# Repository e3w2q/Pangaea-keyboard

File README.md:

# Pangaea

Parts adjustable keyboard

## What is Pangaea?

Column staggered keyboards differ in the way the columns are shifted and the thumb keys are placed, depending on the designer's assumed finger size and design philosophy.

Pangaea is a column staggered keyboard that allows you to adjust the key layout for the pinky and thumb areas.

https://user-images.githubusercontent.com/50942793/145424793-fb12e412-2e66-4725-97fb-f4ba11a33d6f.mp4

## Link

[ホワイトペーパー](whitepaper_jp.md), [White Paper](whitepaper_en.md)

[ビルドガイド](build_guide_jp.md), [Build Guide](build_guide_en.md)

[パーツリスト](bom_list_jp.md)

[Firmware](firmware/)

[PCB](design/)

[Gerbers](products/)

## License

* firmware: GPLv3
* Garber files: CC-BY-NC
* other files: MIT

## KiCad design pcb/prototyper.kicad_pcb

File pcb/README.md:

# Pangaea PCB Data

Some design data are not included.

“Further, we have to be prepared always for the possibility that each new discovery, no matter what science furnishes it, may modify the conclusions we draw.” 

Alfred Wegener, *The Origins of Continents and Oceans*

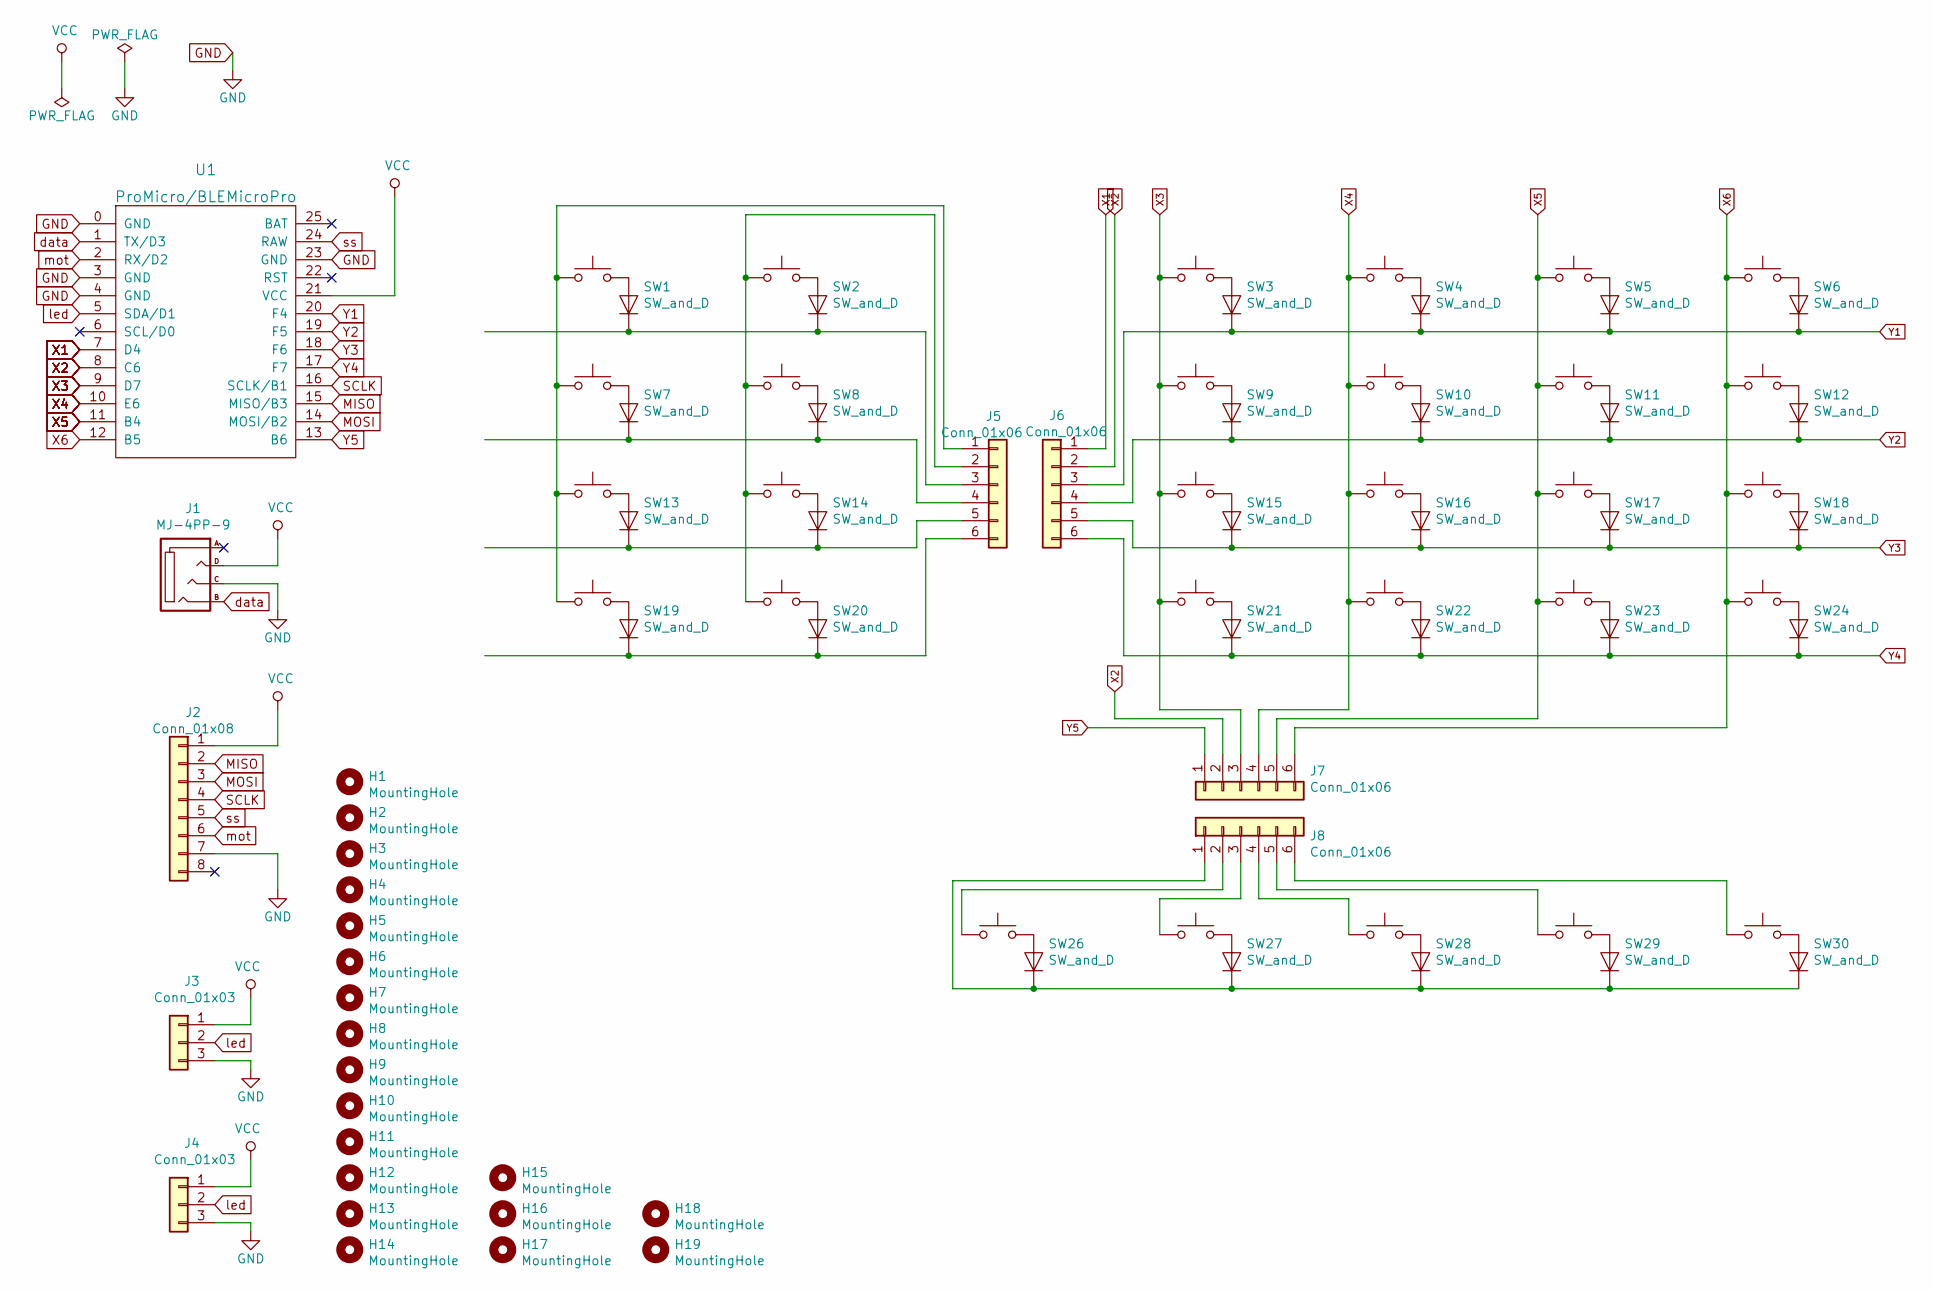
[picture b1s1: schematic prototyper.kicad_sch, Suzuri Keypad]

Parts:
H1, H2, H3, H4, H5, H6, H7, H8, H9, H10, H11, H12, H13, H14: MountingHole; M2_spacer
H15, H16, H17, H18, H19: MountingHole; M1.4_tapping_Hole_rev2
J1: MJ-4PP-9; MJ-4PP-9_reversible
J2: Conn_01x08; PinHeader_1x08_P2.54mm_Vertical_rev2
J3, J4: Conn_01x03; StripLED_rev3
J5, J6, J7, J8: Conn_01x06; PinHeader_1x06_P2.54mm_Vertical_rev2
SW1, SW2, SW3, SW4, SW5, SW6, SW7, SW8, SW9, SW10, SW11, SW12, SW13, SW14, SW15, SW16, SW17, SW18, SW19, SW20, SW21, SW22, SW23, SW24, SW26, SW27, SW28, SW29, SW30: SW_and_D; CherryMX_MidHeight_Choc_Hotswap_Reversible_with_Diode
U1: ProMicro/BLEMicroPro; ArduinoProMicro_ConThrough_Reversible

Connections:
GND: J1.C, J2.7, J3.3, J4.3, U1.0 (GND), U1.3 (GND), U1.4 (GND), U1.23 (GND)
MISO: J2.2, U1.15 (MISO/B3)
MOSI: J2.3, U1.14 (MOSI/B2)
unnamed: J5.1, SW1.1, SW7.1, SW13.1, SW19.1
unnamed: J5.2, SW2.1, SW8.1, SW14.1, SW20.1
unnamed: J5.3, SW1.2, SW2.2
unnamed: J5.4, SW7.2, SW8.2
unnamed: J5.5, SW13.2, SW14.2
unnamed: J5.6, SW19.2, SW20.2
unnamed: J8.1, SW26.2, SW27.2, SW28.2, SW29.2, SW30.2
unnamed: J8.2, SW26.1
unnamed: J8.3, SW27.1
unnamed: J8.4, SW28.1
unnamed: J8.5, SW29.1
unnamed: J8.6, SW30.1
SCLK: J2.4, U1.16 (SCLK/B1)
VCC: J1.D, J2.1, J3.1, J4.1, U1.21 (VCC)
X1: J6.1, U1.7 (D4)
X2: J6.2, J7.2, U1.8 (C6)
X3: J7.3, SW3.1, SW9.1, SW15.1, SW21.1, U1.9 (D7)
X4: J7.4, SW4.1, SW10.1, SW16.1, SW22.1, U1.10 (E6)
X5: J7.5, SW5.1, SW11.1, SW17.1, SW23.1, U1.11 (B4)
X6: J7.6, SW6.1, SW12.1, SW18.1, SW24.1, U1.12 (B5)
Y1: J6.3, SW3.2, SW4.2, SW5.2, SW6.2, U1.20 (F4)
Y2: J6.4, SW9.2, SW10.2, SW11.2, SW12.2, U1.19 (F5)
Y3: J6.5, SW15.2, SW16.2, SW17.2, SW18.2, U1.18 (F6)
Y4: J6.6, SW21.2, SW22.2, SW23.2, SW24.2, U1.17 (F7)
Y5: J7.1, U1.13 (B6)
data: J1.B, U1.1 (TX/D3)
led: J3.2, J4.2, U1.5 (SDA/D1)
mot: J2.6, U1.2 (RX/D2)
ss: J2.5, U1.24 (RAW)

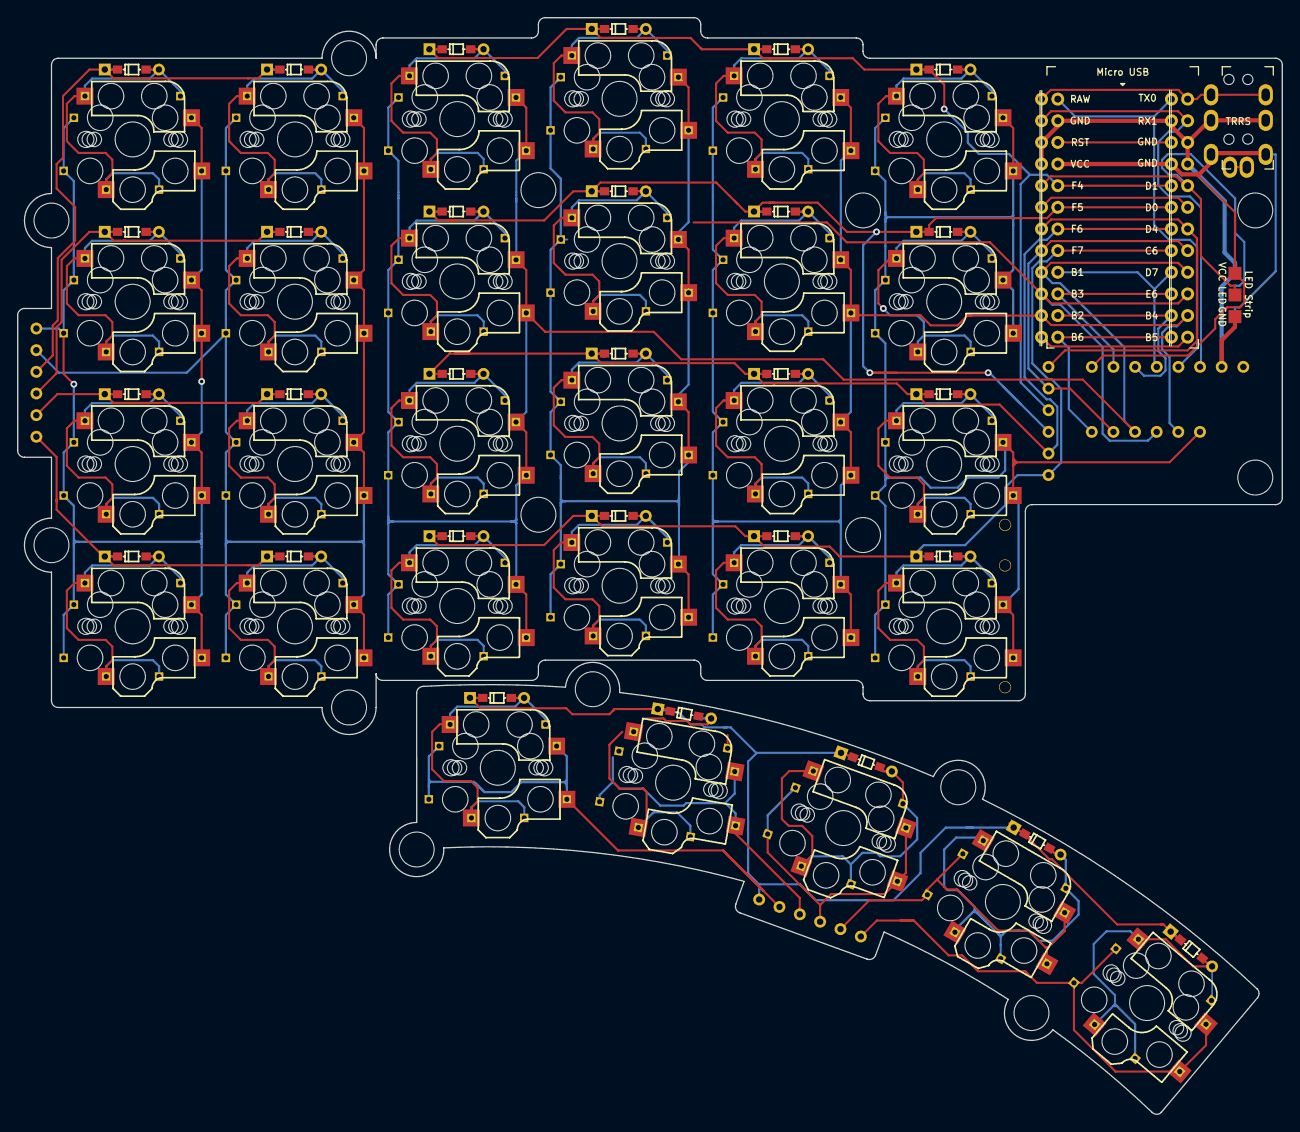
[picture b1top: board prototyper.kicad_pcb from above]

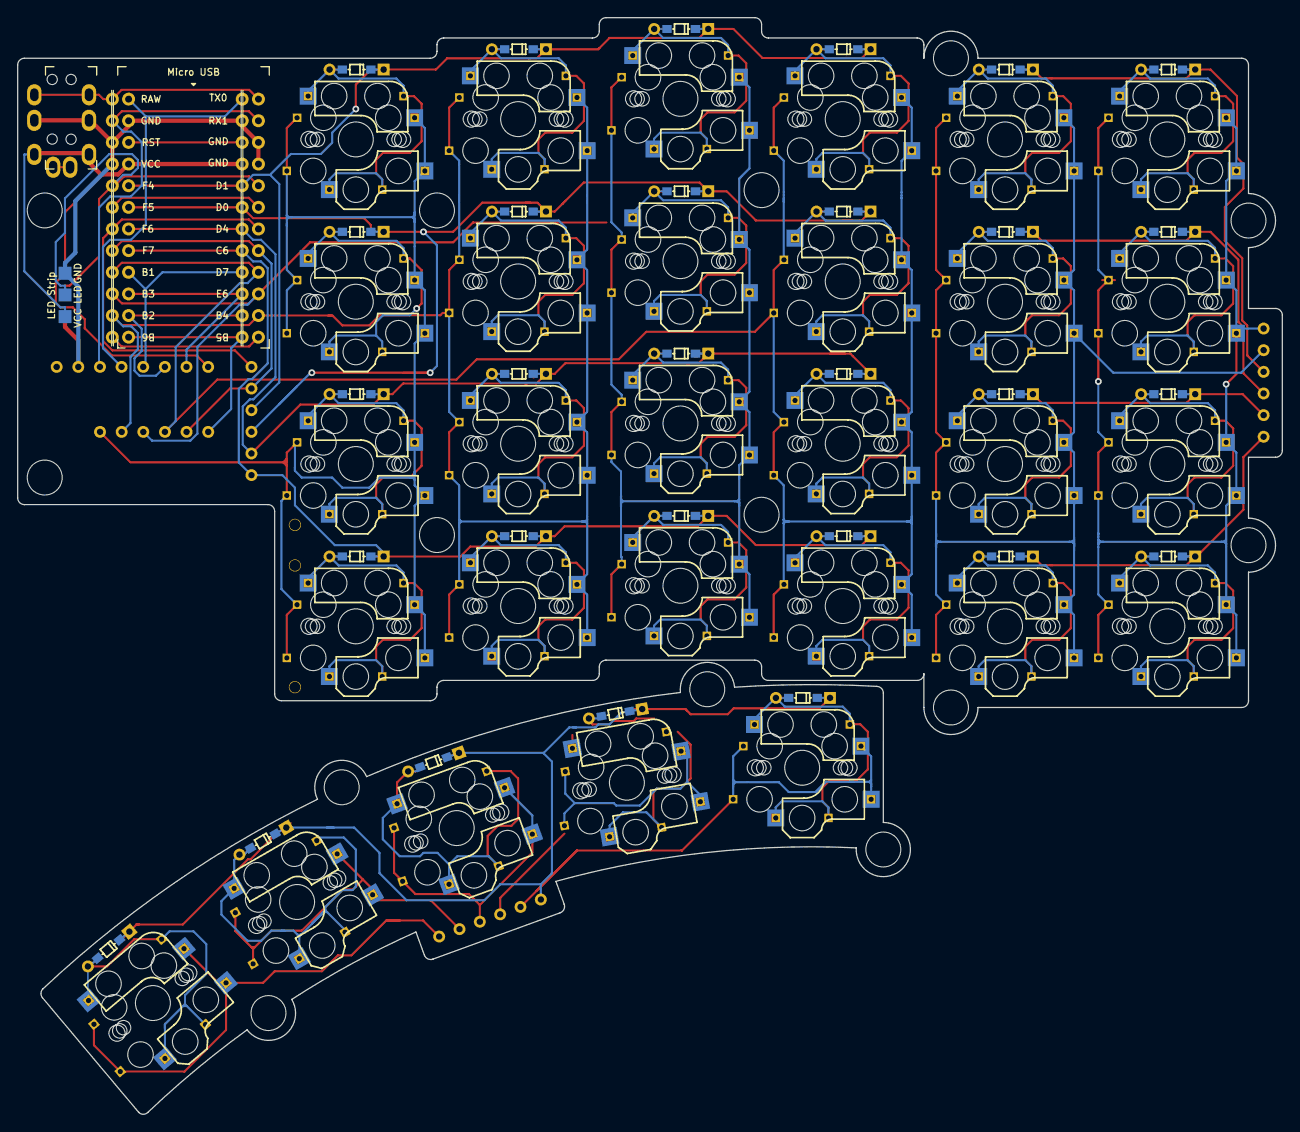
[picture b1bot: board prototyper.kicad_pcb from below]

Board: 2 copper layers, 148.4 x 128.7 mm, 55 parts (2 on the bottom side), 32 nets.

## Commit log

2021-07-25 move documents
2021-07-25 Update pangaea-specification-1.0.md
    ititial
2021-07-25 Update pangaea-specification-1.0.md
    Added switches.
2021-07-25 Update pangaea-specification-1.0.md
    Added APPENDIX C.
2021-07-27 add firmware
    qmk keyboard skeleton
2021-07-28 fix LAYOUT macro function
    disabled VIA, and changed default keymap for debugging.
2021-07-31 Added APPENDIX D - implementation example
    layouts example with Keyboard Layout Editor
2021-07-31 Added Thumb 1 and 2
2021-07-31 Added main layout-1
2021-09-09 Upload PCB
2021-09-11 firmware 0.2
2021-09-11 Countermeasures for bootmagic function
2021-09-11 Update firmware
2021-09-25 Rewrite the firmware to use a custom matrix.
2021-10-03 Update keymap.c
    initial values for EEPROM
2021-10-03 Update hex
2021-10-04 Update via json
2021-11-23 Update firmware (v1.0)
2021-12-04 Update White paper
2021-12-04 Fix White paper
2021-12-04 Update Images for white paper
2021-12-04 fix jpg to jpeg
2021-12-04 Adjust image size
2021-12-05 video added
2021-12-09 Update documents
2021-12-10 Fix build guide
2021-12-12 Add ProMicro image
2021-12-12 Update build guide
    add section of promicro putting
2021-12-12 test
2021-12-12 Added SMD diode photo and explanation.
2021-12-12 Added texts without pictures
2021-12-12 Update build_guide_jp.md
    ・用語確認の写真の位置と改行を修正
    ・不要と思われる｀｀の削除
2021-12-13 Relapaced left handed wired image
2021-12-13 replaced left hand wired picture
2021-12-13 removed a picture of all left parts
2021-12-13 removed a picture of SMD diode
2021-12-13 Added picture of PCB wrench
2021-12-13 added a picture of stando-off
2021-12-13 Update build guide
    change images, arrange sections order
2021-12-13 Update buildguide
2021-12-16 Update build_guide_jp.md
    不要と思われる記号を削除
2021-12-24 #13 Indicate the rubber feet position in the build guide
2022-11-12 Update pangaea.json
    update via definition json (v.1.0)
2022-11-12 enable LED effect
2022-11-25 update build guide
2022-11-27 fix links and detail layout
2022-12-04 first
2022-12-04 update 1.2 via
2022-12-04 Explicit license details
2022-12-04 fixed links.
2022-12-04 fixed link.
2022-12-04 fixed links
2022-12-04 fixed erros.
2022-12-05 replace 2 images on the top of build guide
2022-12-05 update illustrations in quick build guide
2022-12-05 Update quick_build_guide.md
    adjusting size of images
2022-12-05 fixed.
    Deleted the old picture of MT3.
2022-12-06 Update build_guide_en.md
    Simplified the text.
2022-12-06 Update build_guide_en.md
    added link
2022-12-06 Create 3mm-8mm-PCB.drawio.png
    png
2022-12-08 layered.
    layered.
2022-12-08 fixed layer.
2022-12-08 moved png jpg
2022-12-08 removed.
2022-12-23 Update build_guide_jp.md
    remove [PHOTO]s
2022-12-24 updated wired expression
2022-12-24 updated the link to the white paper(JP)
2022-12-24 v1.2
2022-12-24 enable RGB in via keymap
2022-12-24 License set up.
2022-12-25 fixed md error
2022-12-26 append size to filename
2022-12-27 Update README.md
    Added logos for each license.
2023-01-06 BOOTMAGIC_ENABLE = lite -->> yes
    for newer qmk_firmware
2023-01-07 Update rules.mk
    BOOTMAGIC_ENABLE = lite ==>> yes
2023-03-01 append about M1.4 holes
2023-03-05 Update bom_list_jp.md
    add M1.4 screw and nut
2023-10-09 minor fix
2023-10-09 add vial keymap
2023-10-24 gitignore add .DS_Store
2023-10-24 remove OLED config from default keymap
2023-10-24 update k2 keymap
2023-10-24 port config in .h and .mk to info.json
2023-10-24 update k2 keymap (encorder sample)
2023-12-20 Apply ENCODER_MAP
2024-04-18 Update config.h
    Define RGBLIGHT_SPLIT and RGB_SPLIT to synchronize the LED state with the left and right hands. Since this would increase the firmware size, the breathing animation was disabled so as not to exceed P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
2024-04-18 Update vial keymap
    The mouse key was disabled to free up space, and the tapping function and LED animation were enabled.

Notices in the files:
README.md:
Gerber:CC-BY-NC
KiCAD design License:MIT
